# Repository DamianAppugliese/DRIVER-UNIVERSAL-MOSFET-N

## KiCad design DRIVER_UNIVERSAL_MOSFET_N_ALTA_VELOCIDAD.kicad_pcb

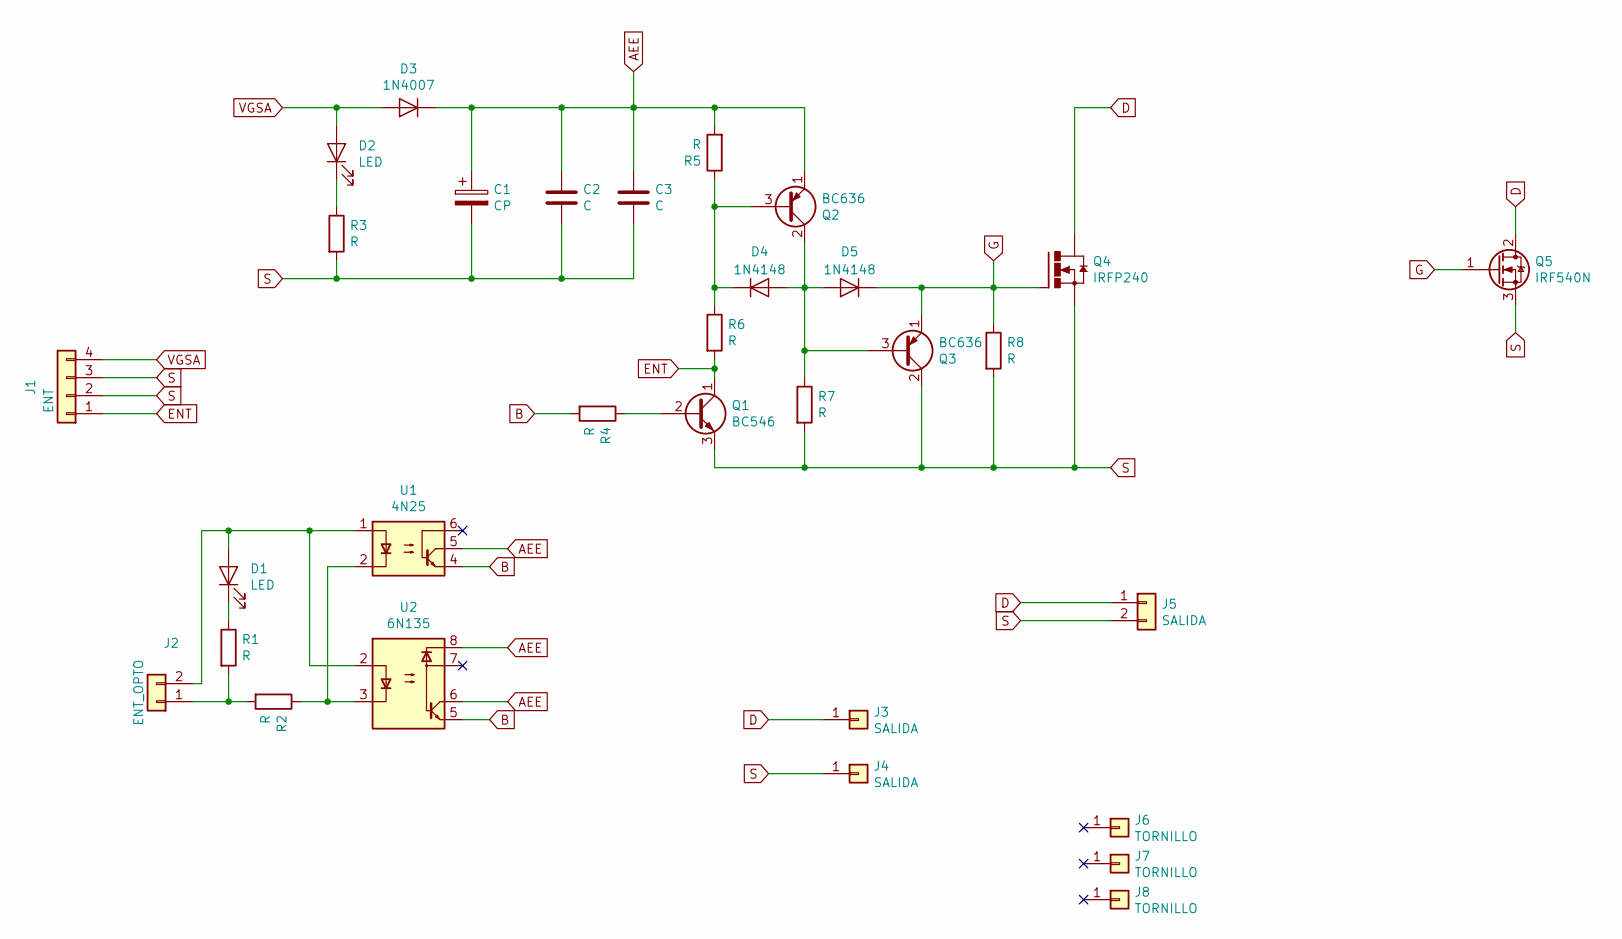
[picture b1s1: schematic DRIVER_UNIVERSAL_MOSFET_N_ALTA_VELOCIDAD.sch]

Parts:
C1: CP; C_Radial_D6.3mm_H5.0mm_P2.50mm
C2, C3: C; C_0603_1608Metric
D1, D2: LED; LED_D3.0mm
D3: 1N4007; D_1206_3216Metric_Pad1.42x1.75mm_HandSolder
D4, D5: 1N4148; D_1206_3216Metric_Pad1.42x1.75mm_HandSolder
J1: ENT; PinHeader_1x04_P2.54mm_Vertical
J2: ENT_OPTO; PinHeader_1x02_P2.54mm_Vertical
J3, J4: SALIDA; MountingHole_4mm_Pad_Via
J5: SALIDA; PhoenixContact_MCV_1,5_2-G-5.08_1x02_P5.08mm_Vertical
J6, J7, J8: TORNILLO; MountingHole_2.7mm_Pad_Via
Q1: BC546; TO-92_Wide
Q2, Q3: BC636; TO-92_Wide
Q4: IRFP240; TO-247-3_Vertical
Q5: IRF540N; TO-220-3_Vertical
R1, R2, R3, R4, R5, R6, R7, R8: R; R_2010_5025Metric
U1: 4N25; DIP-6_W7.62mm
U2: 6N135; DIP-8_W7.62mm

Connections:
AEE: C1.1, C2.1, C3.1, D3.1 (K), Q2.1 (E), R5.2, U1.5, U2.6, U2.8
B: R4.2, U1.4, U2.5
D: J3.1, J5.1, Q4.2 (D), Q5.2 (D)
ENT: J1.1, Q1.1 (C), R6.2
G: D5.1 (K), Q3.1 (E), Q4.1 (G), Q5.1 (G), R8.1
unnamed: D1.1 (K), R1.1
unnamed: D1.2 (A), J2.2, U1.1, U2.2
unnamed: D2.1 (K), R3.1
unnamed: D4.1 (K), Q2.3 (B), R5.1, R6.1
unnamed: D4.2 (A), D5.2 (A), Q2.2 (C), Q3.3 (B), R7.1
unnamed: J2.1, R1.2, R2.2
unnamed: Q1.2 (B), R4.1
unnamed: R2.1, U1.2, U2.3
S: C1.2, C2.2, C3.2, J1.2, J1.3, J4.1, J5.2, Q1.3 (E), Q3.2 (C), Q4.3 (S), Q5.3 (S), R3.2, R7.2, R8.2
VGSA: D2.2 (A), D3.2 (A), J1.4

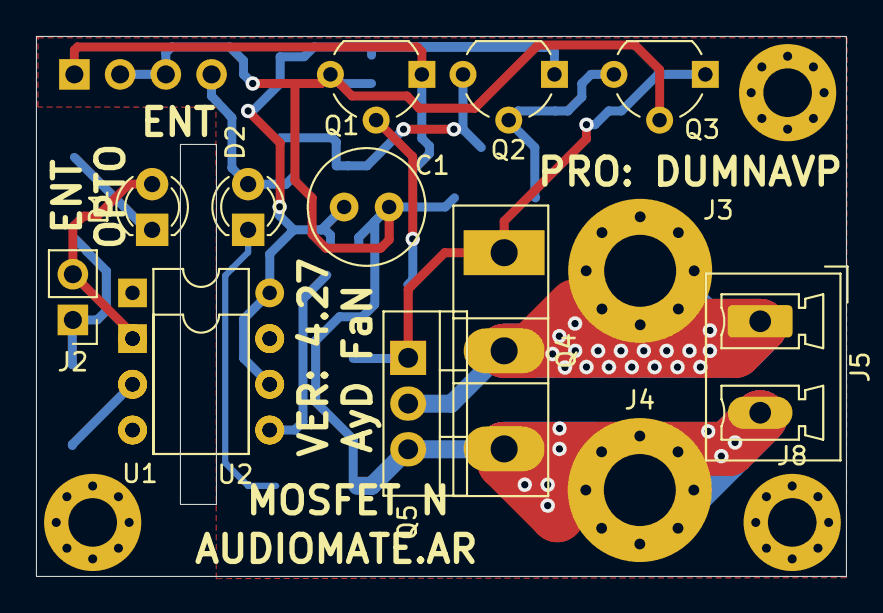
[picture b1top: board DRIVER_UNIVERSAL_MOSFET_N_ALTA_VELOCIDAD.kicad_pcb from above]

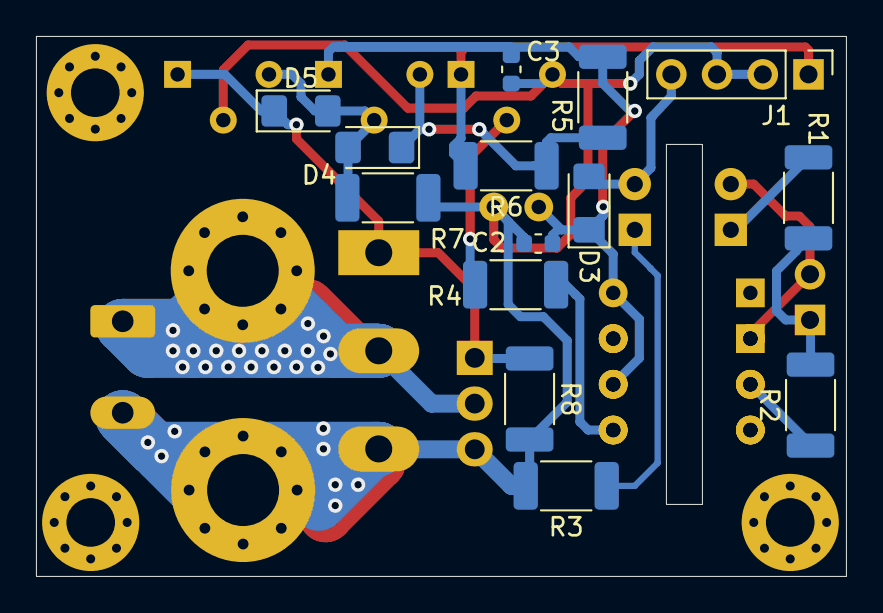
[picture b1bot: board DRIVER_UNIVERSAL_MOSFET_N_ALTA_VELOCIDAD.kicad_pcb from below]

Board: 2 copper layers, 45.0 x 30.0 mm, 31 parts (14 on the bottom side), 15 nets.
